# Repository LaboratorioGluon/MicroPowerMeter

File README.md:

# MicroPowerMeter

This repo contains the Hardware design of my version of a low current meter (from nanoamperes to milliamperes).

More Info [Blog Entry](https://en.laboratoriogluon.com/projects/micropowermeter/).

## Capabilities

- 4 kSps
- 3 Ranges: nA, uA and mA.
- Automatic range switching
- USB connection.
- Low Burden Voltage:
    - 10 uV/nA 
    - 10 uV/uA
    - 10 uV/mA

## Electrical characteristics

- TBD

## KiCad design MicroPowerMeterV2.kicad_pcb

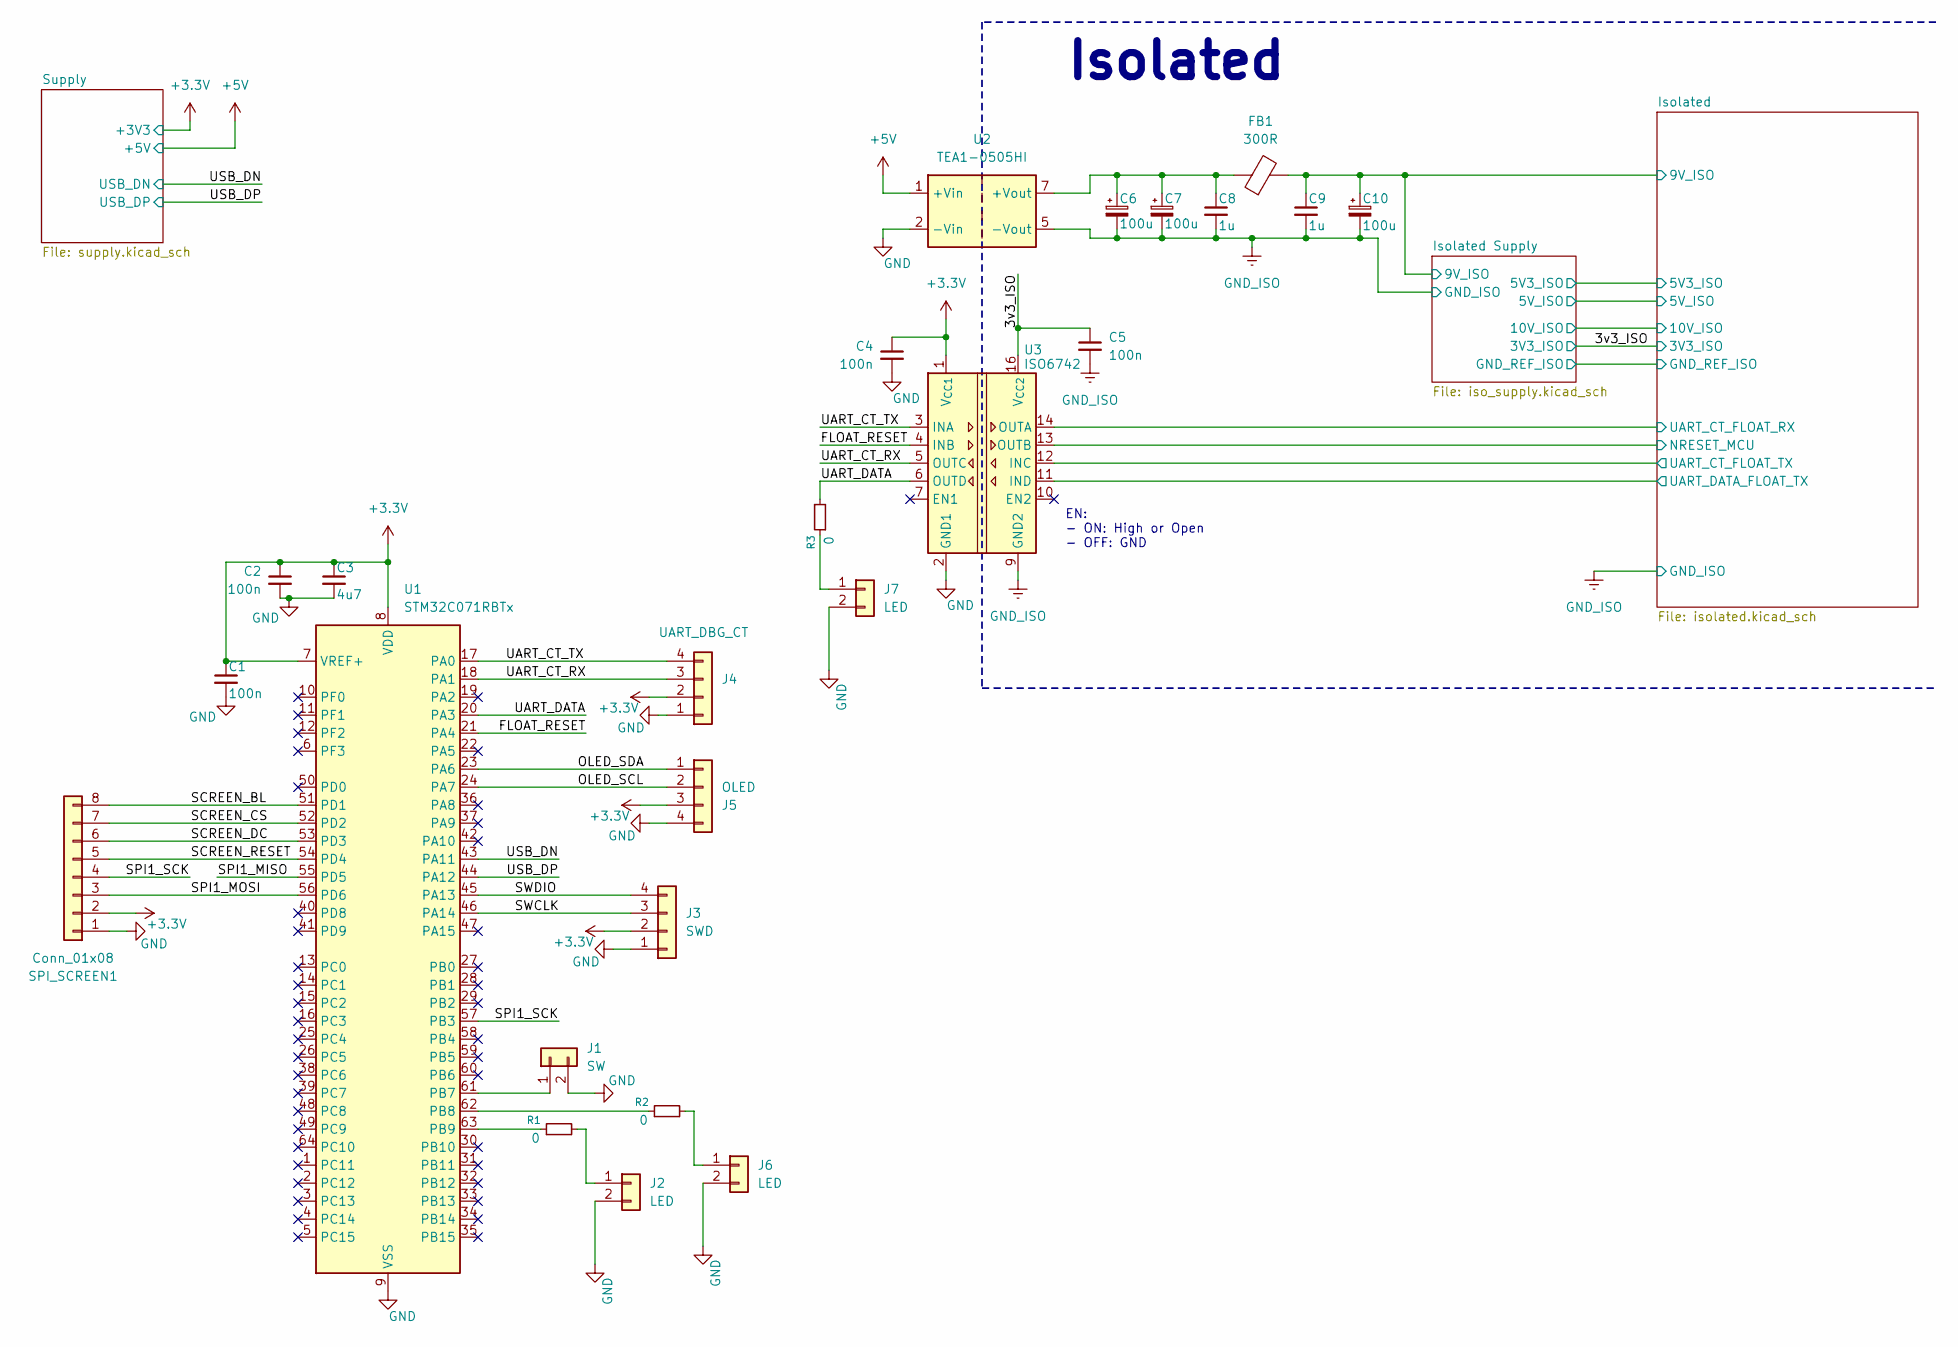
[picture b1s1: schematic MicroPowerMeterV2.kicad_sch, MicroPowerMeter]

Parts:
C1, C2, C4, C5: 100n; C_0603_1608Metric
C3: 4u7; C_0603_1608Metric
C6, C7: 100u; CP_Elec_6.3x5.4
C8, C9: 1u; C_0603_1608Metric
C10: 100u; C_0603_1608Metric
FB1: 300R; L_0603_1608Metric; PartNumber MMZ1608S301ATA00
J1: SW; PinHeader_1x02_P2.54mm_Vertical
J2, J6, J7: LED; PinHeader_1x02_P2.54mm_Vertical
J3: SWD; PinHeader_1x04_P2.54mm_Vertical
J4: UART_DBG_CT; PinHeader_1x04_P2.54mm_Vertical
J5: OLED; OLED_0.96_footprint
R1, R2, R3: 0; R_0603_1608Metric
SPI_SCREEN1: Conn_01x08; PinHeader_1x08_P2.54mm_Vertical
U1: STM32C071RBTx; LQFP-64_10x10mm_P0.5mm
U2: TEA1-0505HI; Converter_DCDC_TRACO_TEA1-xxxxHI_THT
U3: ISO6742; SOIC-16W_7.5x10.3mm_P1.27mm

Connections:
+3.3V: C1.1, C2.1, C3.1, C4.1, J3.2, J4.2, J5.3, SPI_SCREEN1.2, U1.7 (VREF+), U1.8 (VDD), U3.1 (V_{CC1}); also elsewhere on the board
+3V3_ISO: C5.1, U3.16 (V_{CC2}); also elsewhere on the board
+5V: U2.1 (+Vin); also elsewhere on the board
/FLOAT_RESET: U1.21 (PA4), U3.4 (INB)
/Isolated/9V_ISO: C9.1, C10.1, FB1.2; also elsewhere on the board
/Isolated/NRESET_MCU: U3.13 (OUTB); also elsewhere on the board
/Isolated/UART_CT_FLOAT_RX: U3.14 (OUTA); also elsewhere on the board
/Isolated/UART_CT_FLOAT_TX: U3.12 (INC); also elsewhere on the board
/Isolated/UART_DATA_FLOAT_TX: U3.11 (IND); also elsewhere on the board
/OLED_SCL: J5.2, U1.24 (PA7)
/OLED_SDA: J5.1, U1.23 (PA6)
/SCREEN_BL: SPI_SCREEN1.8, U1.51 (PD1)
/SCREEN_CS: SPI_SCREEN1.7, U1.52 (PD2)
/SCREEN_DC: SPI_SCREEN1.6, U1.53 (PD3)
/SCREEN_RESET: SPI_SCREEN1.5, U1.54 (PD4)
/SPI1_MISO: U1.55 (PD5)
/SPI1_MOSI: SPI_SCREEN1.3, U1.56 (PD6)
/SPI1_SCK: SPI_SCREEN1.4, U1.57 (PB3)
/SWCLK: J3.3, U1.46 (PA14)
/SWDIO: J3.4, U1.45 (PA13)
/UART_CT_RX: J4.3, U1.18 (PA1), U3.5 (OUTC)
/UART_CT_TX: J4.4, U1.17 (PA0), U3.3 (INA)
/UART_DATA: R3.2, U1.20 (PA3), U3.6 (OUTD)
/USB_DN: U1.43 (PA11); also elsewhere on the board
/USB_DP: U1.44 (PA12); also elsewhere on the board
GND: C1.2, C2.2, C3.2, C4.2, J1.2, J2.2, J3.1, J4.1, J5.4, J6.2, J7.2, SPI_SCREEN1.1, U1.9 (VSS), U2.2 (-Vin), U3.2 (GND1), U3.8 (GND1); also elsewhere on the board
GND_ISO: C5.2, C6.2, C7.2, C8.2, C9.2, C10.2, U2.5 (-Vout), U3.9 (GND2), U3.15 (GND2); also elsewhere on the board
unnamed: J1.1, U1.61 (PB7)
unnamed: J2.1, R1.2
unnamed: J6.1, R2.2
unnamed: J7.1, R3.1
unnamed: R2.1, U1.62 (PB8)
unnamed: R1.1, U1.63 (PB9)
unnamed: C6.1, C7.1, C8.1, FB1.1, U2.7 (+Vout)

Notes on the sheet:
Isolated
EN: - ON: High or Open - OFF: GND

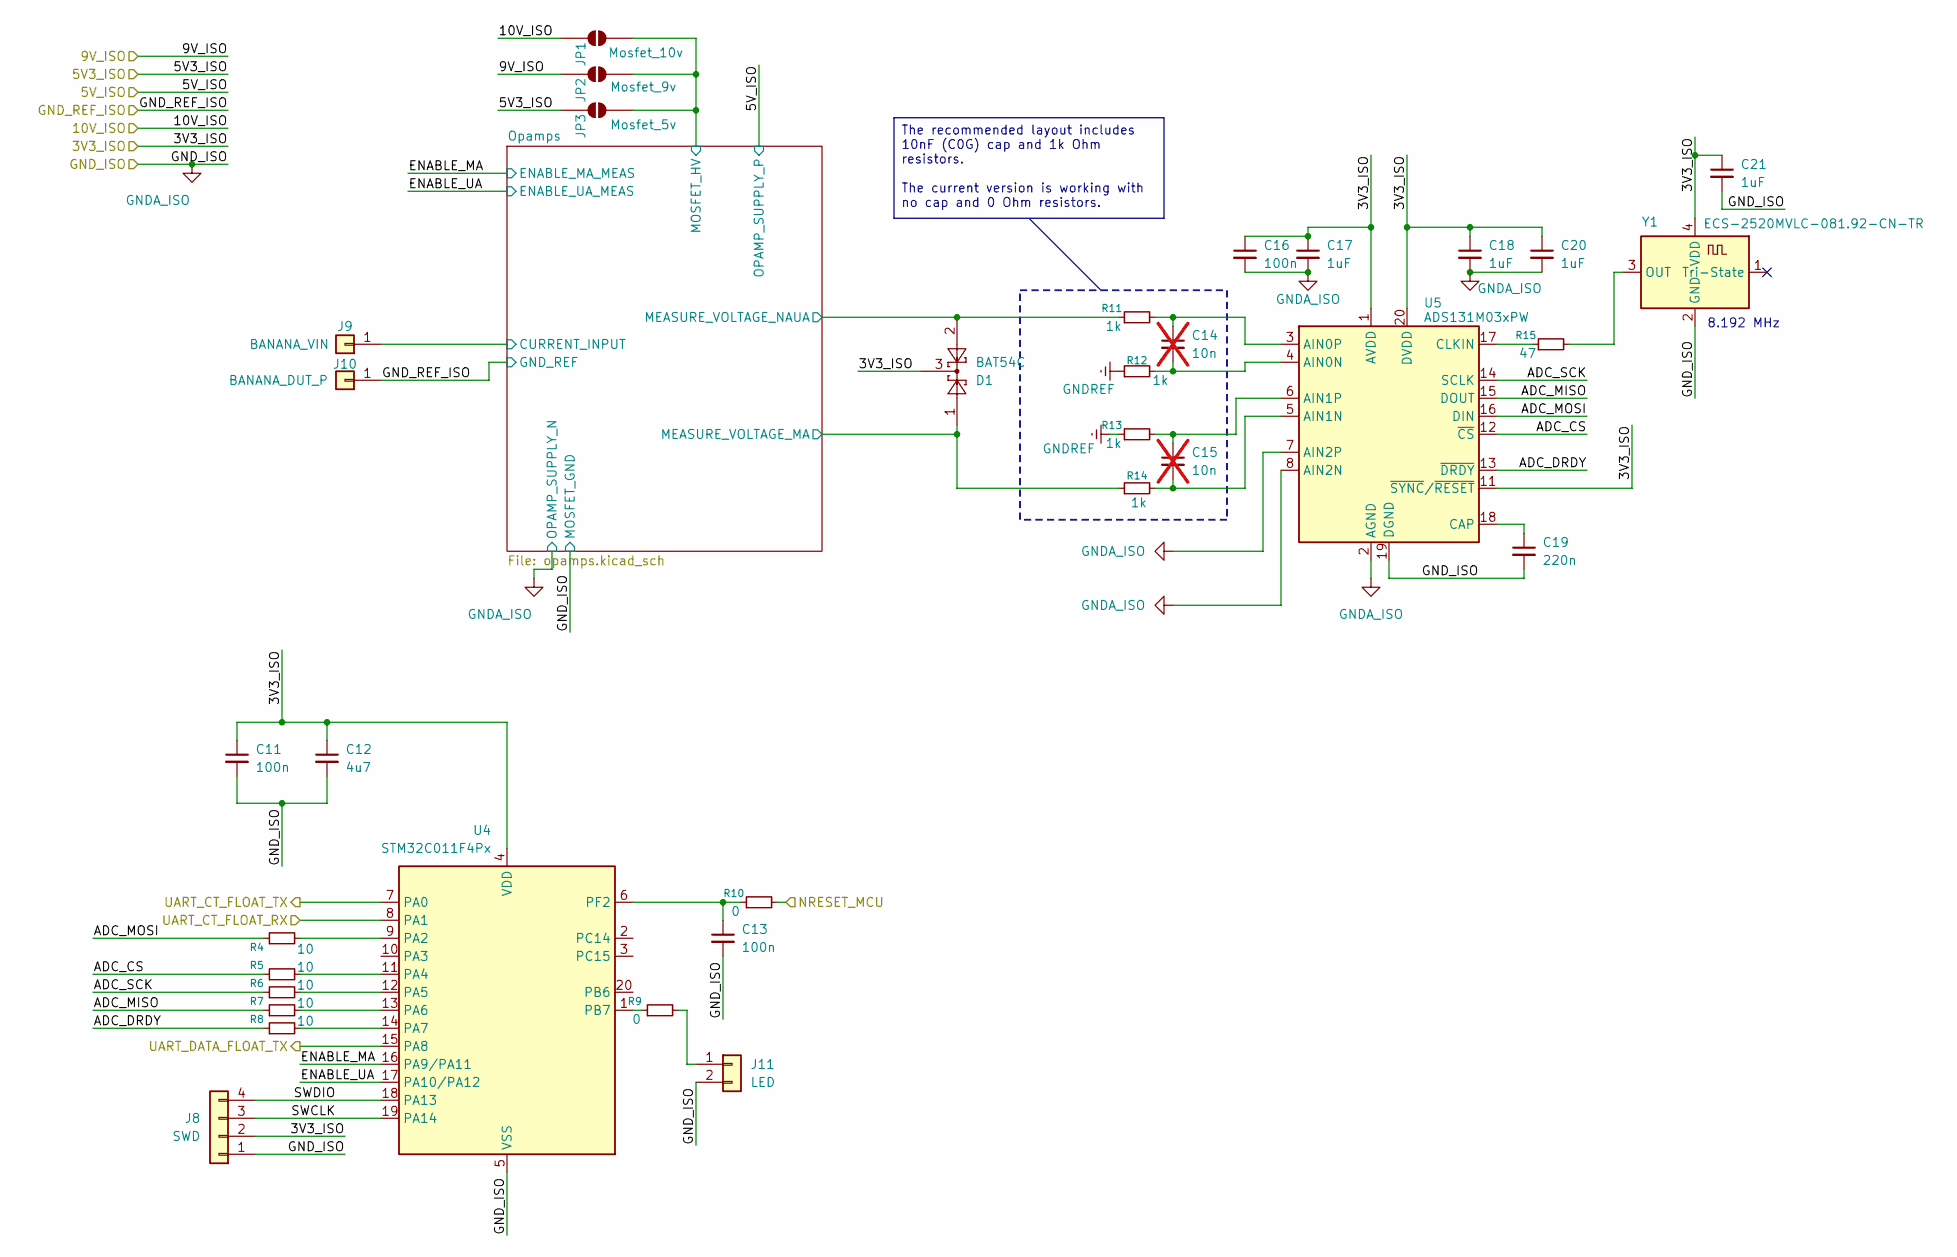
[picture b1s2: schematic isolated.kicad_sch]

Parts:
C11, C13, C16: 100n; C_0603_1608Metric_Pad1.08x0.95mm_HandSolder
C12: 4u7; C_0603_1608Metric_Pad1.08x0.95mm_HandSolder
C14, C15: 10n; C_0603_1608Metric_Pad1.08x0.95mm_HandSolder; not fitted
C17, C18, C20, C21: 1uF; C_0603_1608Metric_Pad1.08x0.95mm_HandSolder
C19: 220n; C_0603_1608Metric_Pad1.08x0.95mm_HandSolder
D1: BAT54C; SOT-23
J8: SWD; PinHeader_1x04_P2.54mm_Vertical
J9: BANANA_VIN; SolderWirePad_1x01_SMD_4x8mm
J10: BANANA_DUT_P; SolderWirePad_1x01_SMD_4x8mm
J11: LED; PinHeader_1x02_P2.54mm_Vertical
JP1: Mosfet_10v; SolderJumper-2_P1.3mm_Open_RoundedPad1.0x1.5mm
JP2: Mosfet_9v; SolderJumper-2_P1.3mm_Open_RoundedPad1.0x1.5mm
JP3: Mosfet_5v; SolderJumper-2_P1.3mm_Open_RoundedPad1.0x1.5mm
R4, R5, R6, R7, R8: 10; R_0603_1608Metric
R9, R10: 0; R_0603_1608Metric
R11, R12, R13, R14: 1k; R_0603_1608Metric
R15: 47; R_0603_1608Metric
U4: STM32C011F4Px; TSSOP-20_4.4x6.5mm_P0.65mm
U5: ADS131M03xPW; TSSOP-20_4.4x6.5mm_P0.65mm
Y1: ECS-2520MVLC-081.92-CN-TR; Oscillator_SMD_ECS_2520MV-xxx-xx-4Pin_2.5x2.0mm

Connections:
+3V3_ISO: C11.1, C12.1, C16.1, C17.1, C18.1, C20.1, C21.1, D1.3, J8.2, U4.4 (VDD), U5.1 (AVDD), U5.11 (~SYNC/~RESET), U5.20 (DVDD), Y1.4 (VDD); also elsewhere on the board
+10V_ISO: JP1.2 (B); also elsewhere on the board
/Isolated Supply/5V3_ISO: JP3.2 (B); also elsewhere on the board
/Isolated/9V_ISO: JP2.2 (B); also elsewhere on the board
/Isolated/ADC_CS: R5.1, U5.12 (~CS)
/Isolated/ADC_DRDY: R8.1, U5.13 (~DRDY)
/Isolated/ADC_MISO: R7.1, U5.15 (DOUT)
/Isolated/ADC_MOSI: R4.1, U5.16 (DIN)
/Isolated/ADC_SCK: R6.1, U5.14 (SCLK)
/Isolated/ENABLE_MA: U4.16 (PA9/PA11); also elsewhere on the board
/Isolated/ENABLE_UA: U4.17 (PA10/PA12); also elsewhere on the board
/Isolated/NRESET_MCU: R10.2; also elsewhere on the board
/Isolated/Opamps/CURRENT_INPUT: J9.1 (Pin_1_1); also elsewhere on the board
/Isolated/Opamps/MEASURE_VOLTAGE_MA: D1.1, R14.1; also elsewhere on the board
/Isolated/Opamps/MEASURE_VOLTAGE_NAUA: D1.2, R11.1; also elsewhere on the board
/Isolated/Opamps/MOSFET_HV: JP1.1 (A), JP2.1 (A), JP3.1 (A); also elsewhere on the board
/Isolated/SWCLK: J8.3, U4.19 (PA14)
/Isolated/SWDIO: J8.4, U4.18 (PA13)
/Isolated/UART_CT_FLOAT_RX: U4.8 (PA1); also elsewhere on the board
/Isolated/UART_CT_FLOAT_TX: U4.7 (PA0); also elsewhere on the board
/Isolated/UART_DATA_FLOAT_TX: U4.15 (PA8); also elsewhere on the board
GNDREF: J10.1 (Pin_1_1), R12.1, R13.1; also elsewhere on the board
GND_ISO: C11.2, C12.2, C13.2, C16.2, C17.2, C18.2, C19.2, C20.2, C21.2, J8.1, J11.2, U4.5 (VSS), U5.2 (AGND), U5.7 (AIN2P), U5.8 (AIN2N), U5.19 (DGND), Y1.2 (GND); also elsewhere on the board
unnamed: J11.1, R9.2
unnamed: R4.2, U4.9 (PA2)
unnamed: R5.2, U4.11 (PA4)
unnamed: R6.2, U4.12 (PA5)
unnamed: R7.2, U4.13 (PA6)
unnamed: R8.2, U4.14 (PA7)
unnamed: R9.1, U4.1 (PB7)
unnamed: C13.1, R10.1, U4.6 (PF2)
unnamed: C14.2, R12.2, U5.4 (AIN0N)
unnamed: C14.1, R11.2, U5.3 (AIN0P)
unnamed: C15.2, R14.2, U5.5 (AIN1N)
unnamed: C15.1, R13.2, U5.6 (AIN1P)
unnamed: C19.1, U5.18 (CAP)
unnamed: R15.1, U5.17 (CLKIN)
unnamed: R15.2, Y1.3 (OUT)

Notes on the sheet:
8.192 MHz
The recommended layout includes 10nF (C0G) cap and 1k Ohm resistors. The current version is working with no cap and 0 Ohm resistors.

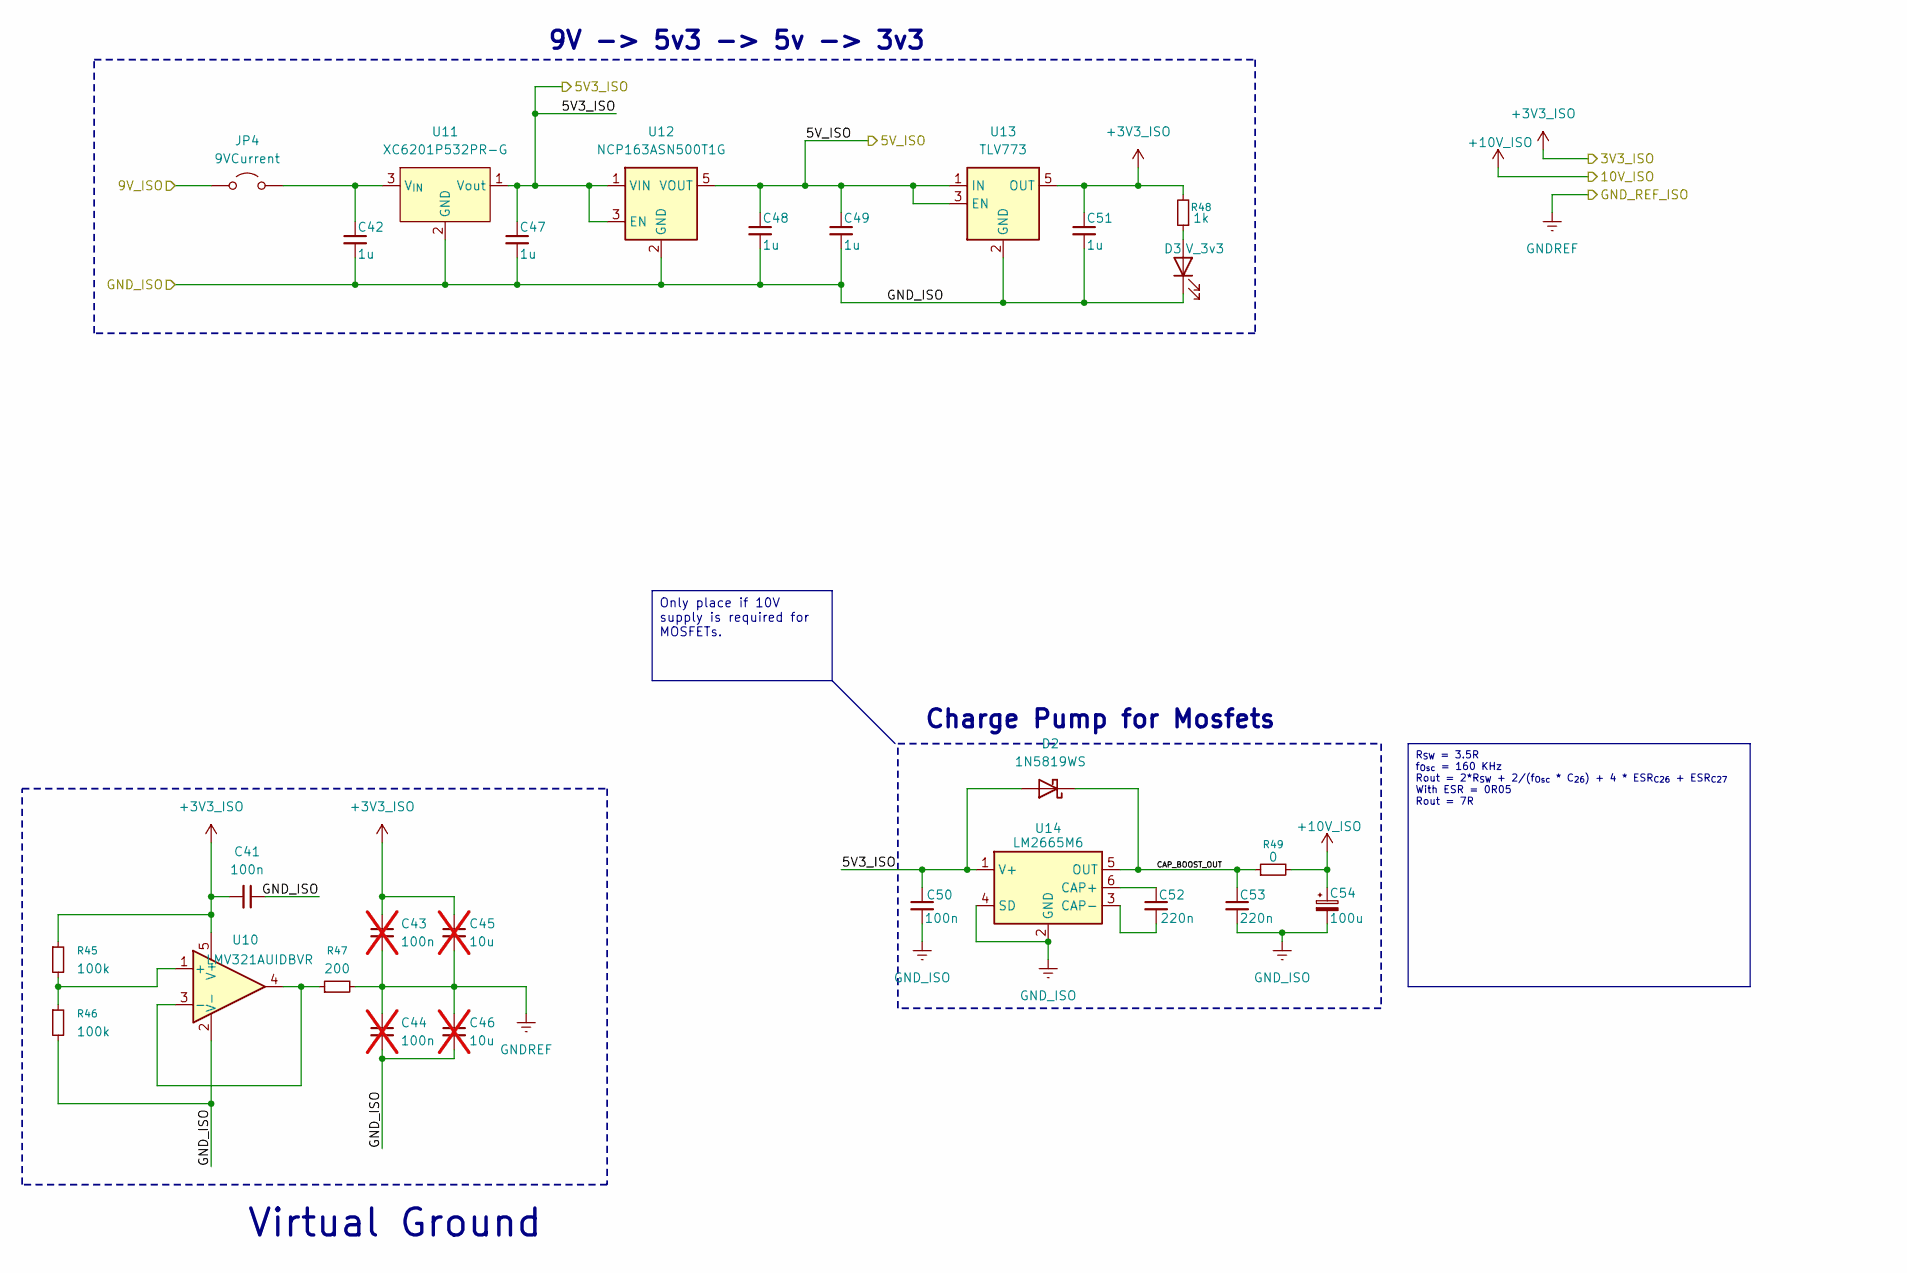
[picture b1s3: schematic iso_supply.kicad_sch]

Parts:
C41, C50: 100n; C_0603_1608Metric
C42, C47, C48, C49, C51: 1u; C_0603_1608Metric
C43, C44: 100n; C_0603_1608Metric; not fitted
C45, C46: 10u; C_0603_1608Metric; not fitted
C52, C53: 220n; C_0603_1608Metric
C54: 100u; CP_Elec_6.3x5.4
D2: 1N5819WS; D_SOD-323_HandSoldering
D3: V_3v3; LED_0603_1608Metric
JP4: 9VCurrent; PinHeader_1x02_P2.54mm_Vertical
R45, R46: 100k; R_0603_1608Metric
R47: 200; R_0603_1608Metric
R48: 1k; R_0603_1608Metric
R49: 0; R_0603_1608Metric
U10: LMV321AUIDBVR; SOT-23-5
U11: XC6201P532PR-G; SOT-89-3
U12: NCP163ASN500T1G; SOT-23-5
U13: TLV773; SOT-23-5
U14: LM2665M6; SOT-23-6; PartNumber LM2665M6X/NOPB

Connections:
+3V3_ISO: C41.2, C43.1, C45.1, C51.1, R45.1, R48.2, U10.5 (V+), U13.5 (OUT); also elsewhere on the board
+10V_ISO: C54.1, R49.2; also elsewhere on the board
/Isolated Supply/5V3_ISO: C47.1, C50.1, D2.2 (A), U11.1 (Vout), U12.1 (VIN), U12.3 (EN), U14.1 (V+); also elsewhere on the board
/Isolated Supply/5V_ISO: C48.1, C49.1, U12.5 (VOUT), U13.1 (IN), U13.3 (EN); also elsewhere on the board
/Isolated Supply/CAP_BOOST_OUT: C53.1, D2.1 (K), R49.1, U14.5 (OUT)
/Isolated/9V_ISO: JP4.1 (A); also elsewhere on the board
GNDREF: C43.2, C44.1, C45.2, C46.1, R47.2; also elsewhere on the board
GND_ISO: C41.1, C42.2, C44.2, C46.2, C47.2, C48.2, C49.2, C50.2, C51.2, C53.2, C54.2, D3.1 (K), R46.2, U10.2 (V-), U11.2 (GND), U12.2 (GND), U13.2 (GND), U13.4 (GND), U14.2 (GND), U14.4 (SD); also elsewhere on the board
unnamed: D3.2 (A), R48.1
unnamed: C42.1, JP4.2 (B), U11.3 (V_{IN})
unnamed: R45.2, R46.1, U10.1 (+)
unnamed: R47.1, U10.3 (-), U10.4
unnamed: C52.1, U14.6 (CAP+)
unnamed: C52.2, U14.3 (CAP-)

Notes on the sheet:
9V -> 5v3 -> 5v -> 3v3
Virtual Ground
Charge Pump for Mosfets
R_{SW} = 3.5R f_{Osc} = 160 KHz Rout = 2*R_{SW} + 2/(f_{Osc} * C_{26}) + 4 * ESR_{C26} + ESR_{C27} With ESR = 0R05 Rout = 7R
Only place if 10V supply is required for MOSFETs.

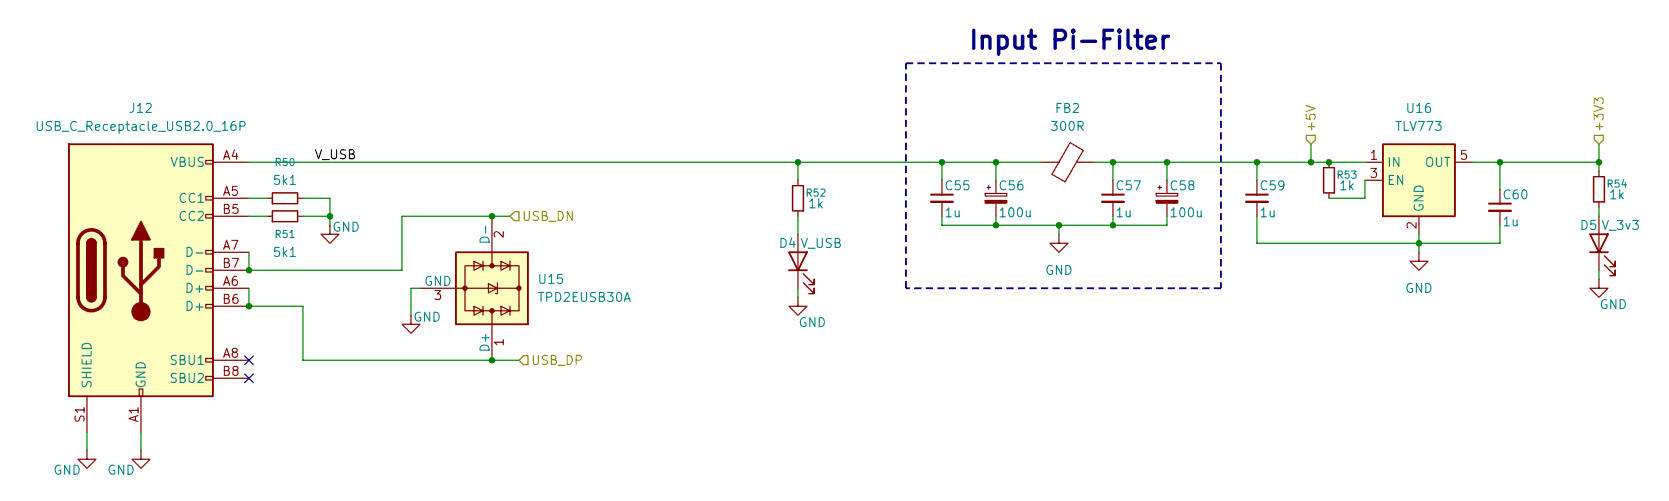
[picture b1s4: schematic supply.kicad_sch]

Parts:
C55, C57, C59, C60: 1u; C_0603_1608Metric
C56, C58: 100u; C_0603_1608Metric
D4: V_USB; LED_0603_1608Metric
D5: V_3v3; LED_0603_1608Metric
FB2: 300R; L_0603_1608Metric; PartNumber MMZ1608S301ATA00
J12: USB_C_Receptacle_USB2.0_16P; USB_C_Receptacle_GCT_USB4105-xx-A_16P_TopMnt_Horizontal
R50, R51: 5k1; R_0603_1608Metric
R52, R53, R54: 1k; R_0603_1608Metric
U15: TPD2EUSB30A; Texas_DRT-3
U16: TLV773; SOT-23-5

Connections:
+3.3V: C60.1, R54.2, U16.5 (OUT); also elsewhere on the board
+5V: C57.1, C58.1, C59.1, FB2.2, R53.2, U16.1 (IN); also elsewhere on the board
/Supply/V_USB: C55.1, C56.1, FB2.1, J12.A4 (VBUS), J12.A9 (VBUS), J12.B4 (VBUS), J12.B9 (VBUS), R52.2
/USB_DN: J12.A7 (D-), J12.B7 (D-), U15.2 (D-); also elsewhere on the board
/USB_DP: J12.A6 (D+), J12.B6 (D+), U15.1 (D+); also elsewhere on the board
GND: C55.2, C56.2, C57.2, C58.2, C59.2, C60.2, D4.1 (K), D5.1 (K), J12.A1 (GND), J12.A12 (GND), J12.B1 (GND), J12.B12 (GND), J12.S1 (SHIELD), R50.2, R51.2, U15.3 (GND), U16.2 (GND), U16.4 (GND); also elsewhere on the board
unnamed: D4.2 (A), R52.1
unnamed: D5.2 (A), R54.1
unnamed: J12.A5 (CC1), R50.1
unnamed: J12.B5 (CC2), R51.1
unnamed: R53.1, U16.3 (EN)

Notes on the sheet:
Input Pi-Filter

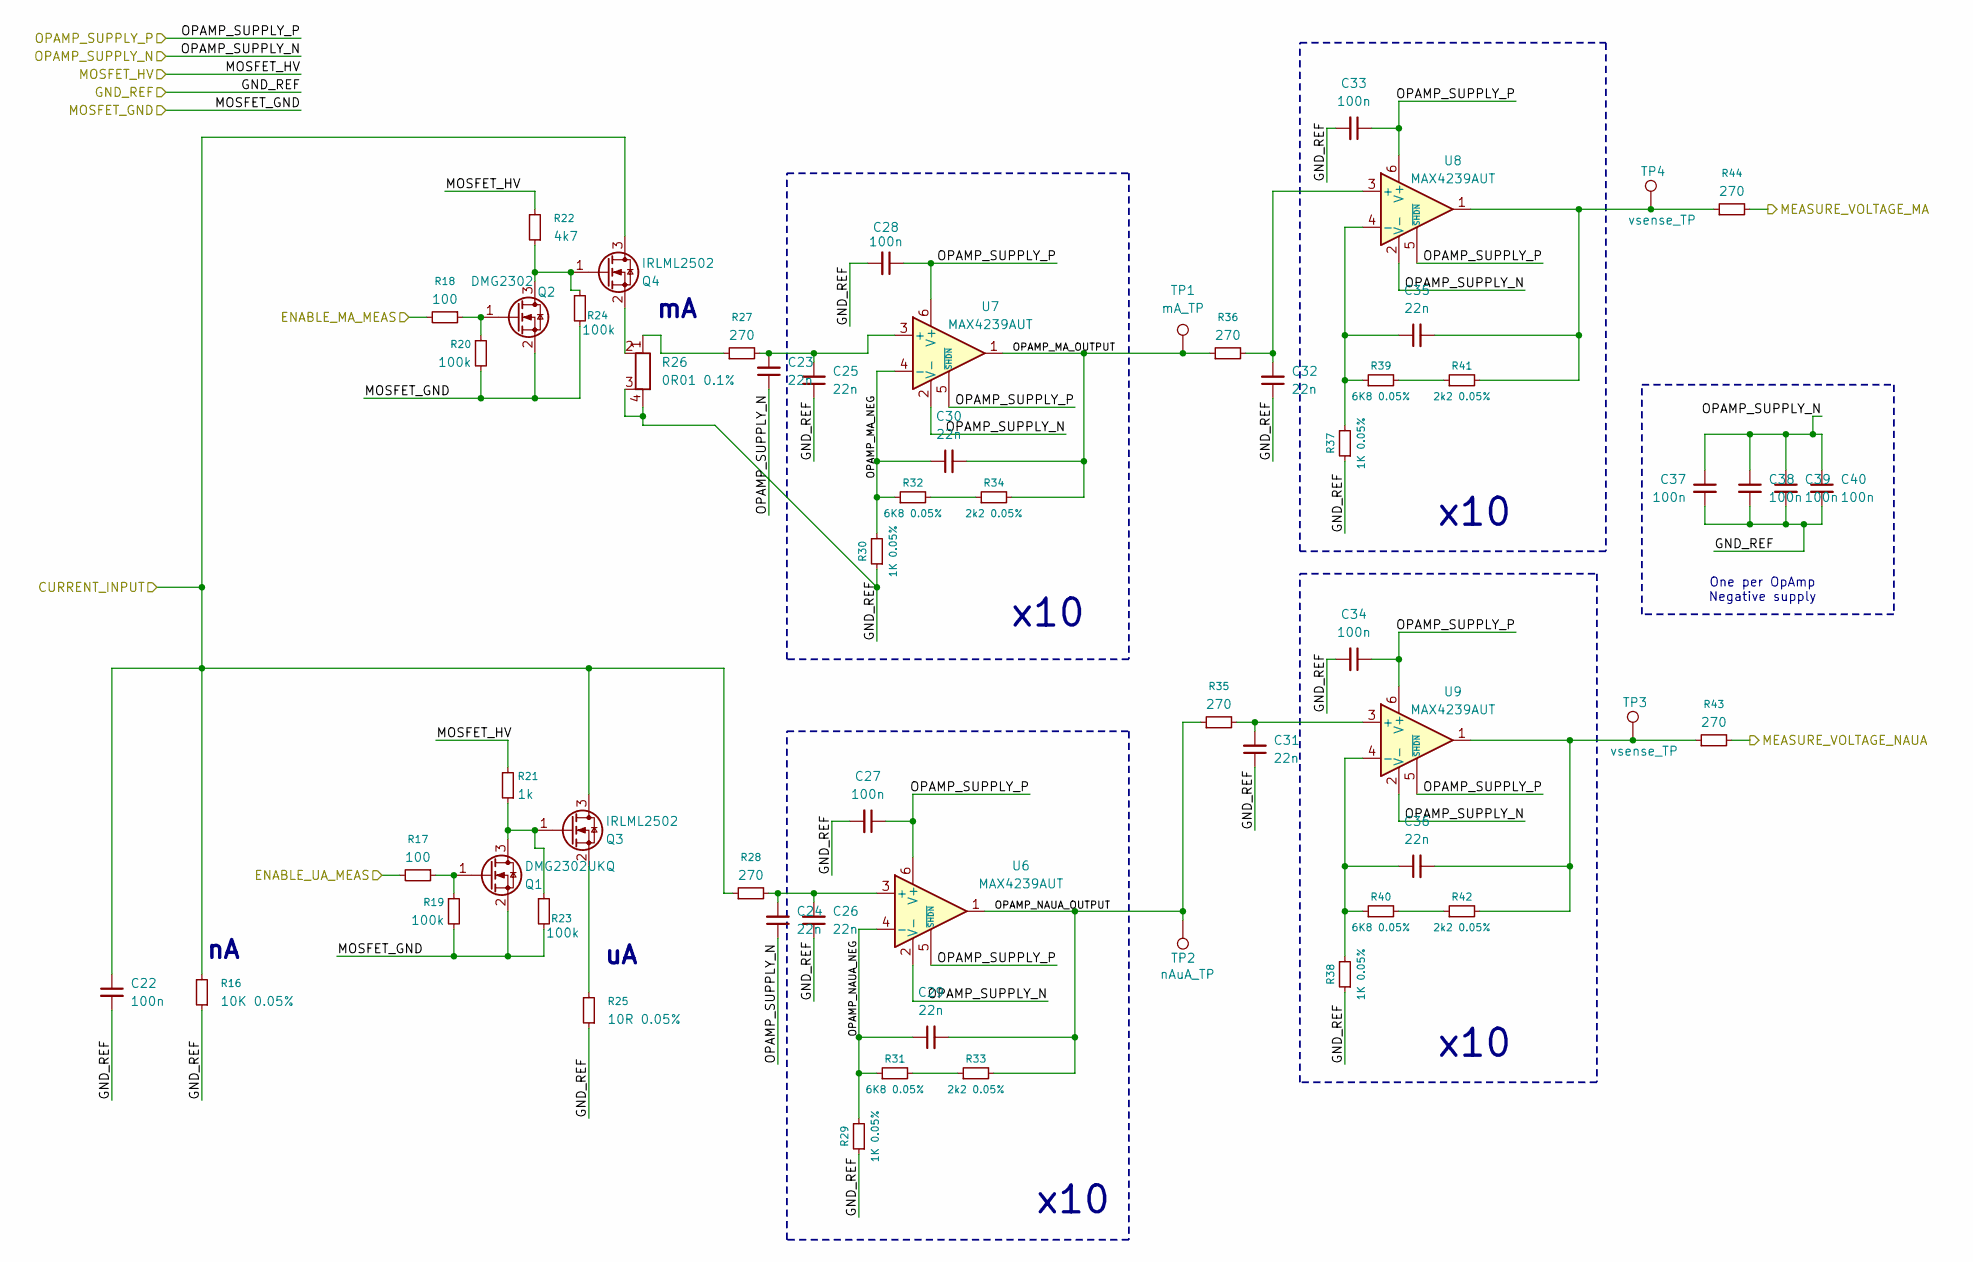
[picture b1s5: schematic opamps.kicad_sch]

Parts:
C22, C27, C28, C33, C34, C37, C38, C39, C40: 100n; C_0603_1608Metric
C23, C24, C25, C26, C29, C30, C31, C32, C35, C36: 22n; C_0603_1608Metric
Q1: DMG2302UKQ; SOT-23; PartNumber IRLML2502TRPBF
Q2: DMG2302; SOT-23; PartNumber IRLML2502TRPBF
Q3, Q4: IRLML2502; SOT-23; PartNumber IRLML2502TRPBF
R16: 10K 0.05%; R_0603_1608Metric; PartNumber RG1608N-103-W-T5
R17, R18: 100; R_0603_1608Metric
R19, R20, R23, R24: 100k; R_0603_1608Metric
R21: 1k; R_0603_1608Metric
R22: 4k7; R_0603_1608Metric
R25: 10R 0.05%; R_0603_1608Metric; PartNumber RNCF0603AKT10R0
R26: 0R01 0.1%; R_Shunt_Ohmite_LVK12; PartNumber LVK12R010DER
R27, R28, R35, R36, R43, R44: 270; R_0603_1608Metric
R29, R30, R37, R38: 1K 0.05%; R_0603_1608Metric; PartNumber RG1608N-102-W-T5
R31, R32, R39, R40: 6K8 0.05%; R_0603_1608Metric; PartNumber RG1608N-682-W-T1
R33, R34, R41, R42: 2k2 0.05%; R_0603_1608Metric; PartNumber RG1608N-222-W-T1
TP1: mA_TP; TestPoint_Pad_D1.0mm
TP2: nAuA_TP; TestPoint_Pad_D1.0mm
TP3, TP4: vsense_TP; TestPoint_Pad_D1.5mm
U6, U7, U8, U9: MAX4239AUT; SOT-23-6; PartNumber MAX4239AUT+T/OPA189IDBVR

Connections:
/Isolated Supply/5V_ISO: C27.1, C28.1, C33.1, C34.1, U6.5 (~SHDN), U6.6 (V+), U7.5 (~SHDN), U7.6 (V+), U8.5 (~SHDN), U8.6 (V+), U9.5 (~SHDN), U9.6 (V+); also elsewhere on the board
/Isolated/ENABLE_MA: R18.2; also elsewhere on the board
/Isolated/ENABLE_UA: R17.2; also elsewhere on the board
/Isolated/Opamps/CURRENT_INPUT: C22.1, Q3.3 (D), Q4.3 (D), R16.2, R28.1; also elsewhere on the board
/Isolated/Opamps/MEASURE_VOLTAGE_MA: R44.2; also elsewhere on the board
/Isolated/Opamps/MEASURE_VOLTAGE_NAUA: R43.2; also elsewhere on the board
/Isolated/Opamps/MOSFET_HV: R21.2, R22.2; also elsewhere on the board
/Isolated/Opamps/OPAMP_MA_NEG: C30.1, R30.2, R32.1, U7.4 (-)
/Isolated/Opamps/OPAMP_MA_OUTPUT: C30.2, R34.2, R36.1, TP1.1 (1_1), U7.1
/Isolated/Opamps/OPAMP_NAUA_NEG: C29.1, R29.2, R31.1, U6.4 (-)
/Isolated/Opamps/OPAMP_NAUA_OUTPUT: C29.2, R33.2, R35.1, TP2.1 (1_1), U6.1
GNDREF: C22.2, C25.1, C26.1, C27.2, C28.2, C31.1, C32.1, C33.2, C34.2, C37.2, C38.2, C39.2, C40.2, R16.1, R25.1, R26.3, R26.4, R29.1, R30.1, R37.1, R38.1; also elsewhere on the board
GND_ISO: C23.1, C24.1, C37.1, C38.1, C39.1, C40.1, Q1.2 (S), Q2.2 (S), R19.2, R20.2, R23.2, R24.2, U6.2 (V-), U7.2 (V-), U8.2 (V-), U9.2 (V-); also elsewhere on the board
unnamed: C35.2, R41.2, R44.1, TP4.1 (1_1), U8.1
unnamed: C36.2, R42.2, R43.1, TP3.1 (1_1), U9.1
unnamed: Q1.3 (D), Q3.1 (G), R21.1, R23.1
unnamed: Q1.1 (G), R17.1, R19.1
unnamed: Q2.3 (D), Q4.1 (G), R22.1, R24.1
unnamed: Q2.1 (G), R18.1, R20.1
unnamed: Q3.2 (S), R25.2
unnamed: Q4.2 (S), R26.2
unnamed: R26.1, R27.1
unnamed: R31.2, R33.1
unnamed: R32.2, R34.1
unnamed: R39.2, R41.1
unnamed: R40.2, R42.1
unnamed: C24.2, C26.2, R28.2, U6.3 (+)
unnamed: C23.2, C25.2, R27.2, U7.3 (+)
unnamed: C32.2, R36.2, U8.3 (+)
unnamed: C35.1, R37.2, R39.1, U8.4 (-)
unnamed: C31.2, R35.2, U9.3 (+)
unnamed: C36.1, R38.2, R40.1, U9.4 (-)

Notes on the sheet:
x10
One per OpAmp Negative supply

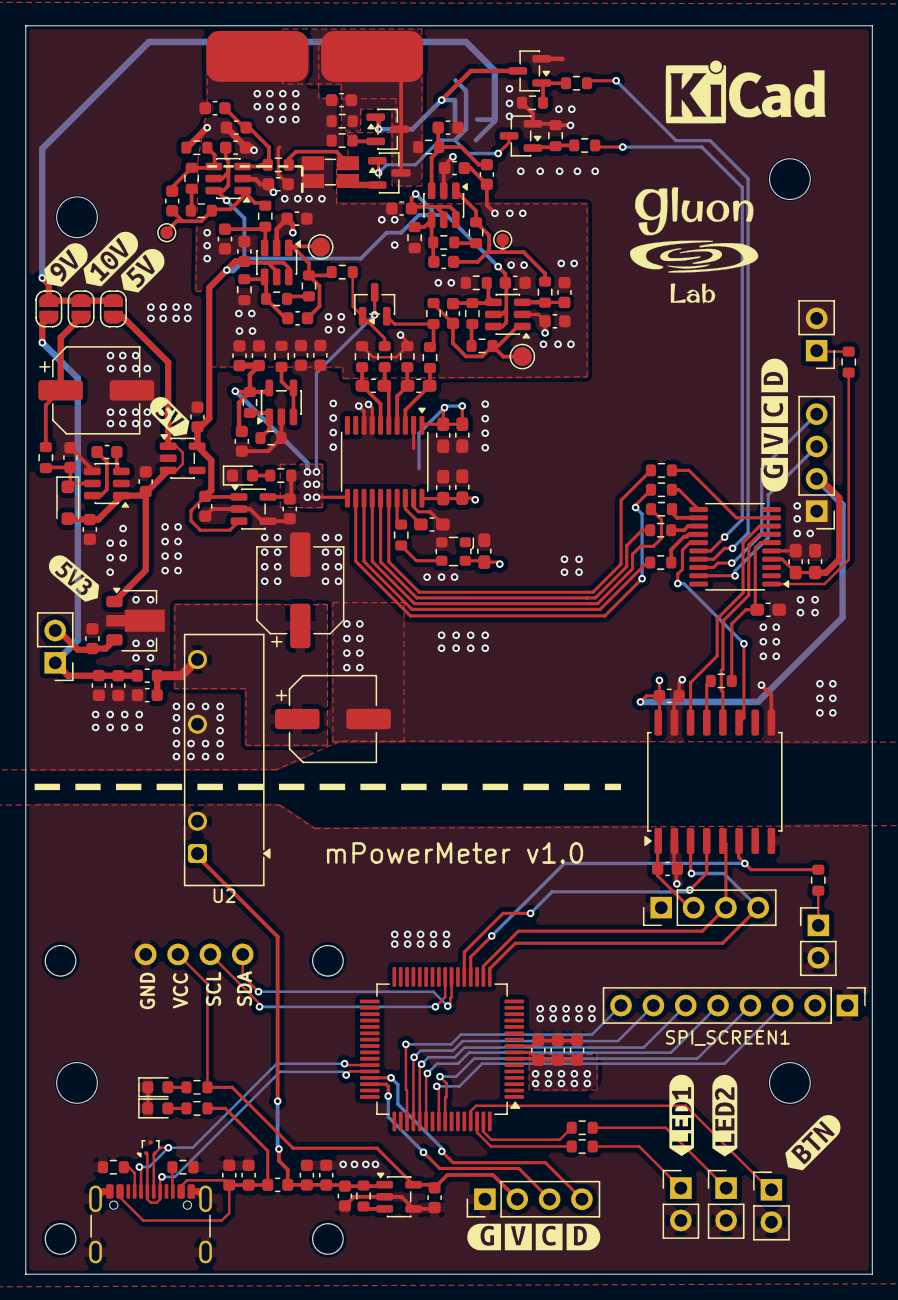
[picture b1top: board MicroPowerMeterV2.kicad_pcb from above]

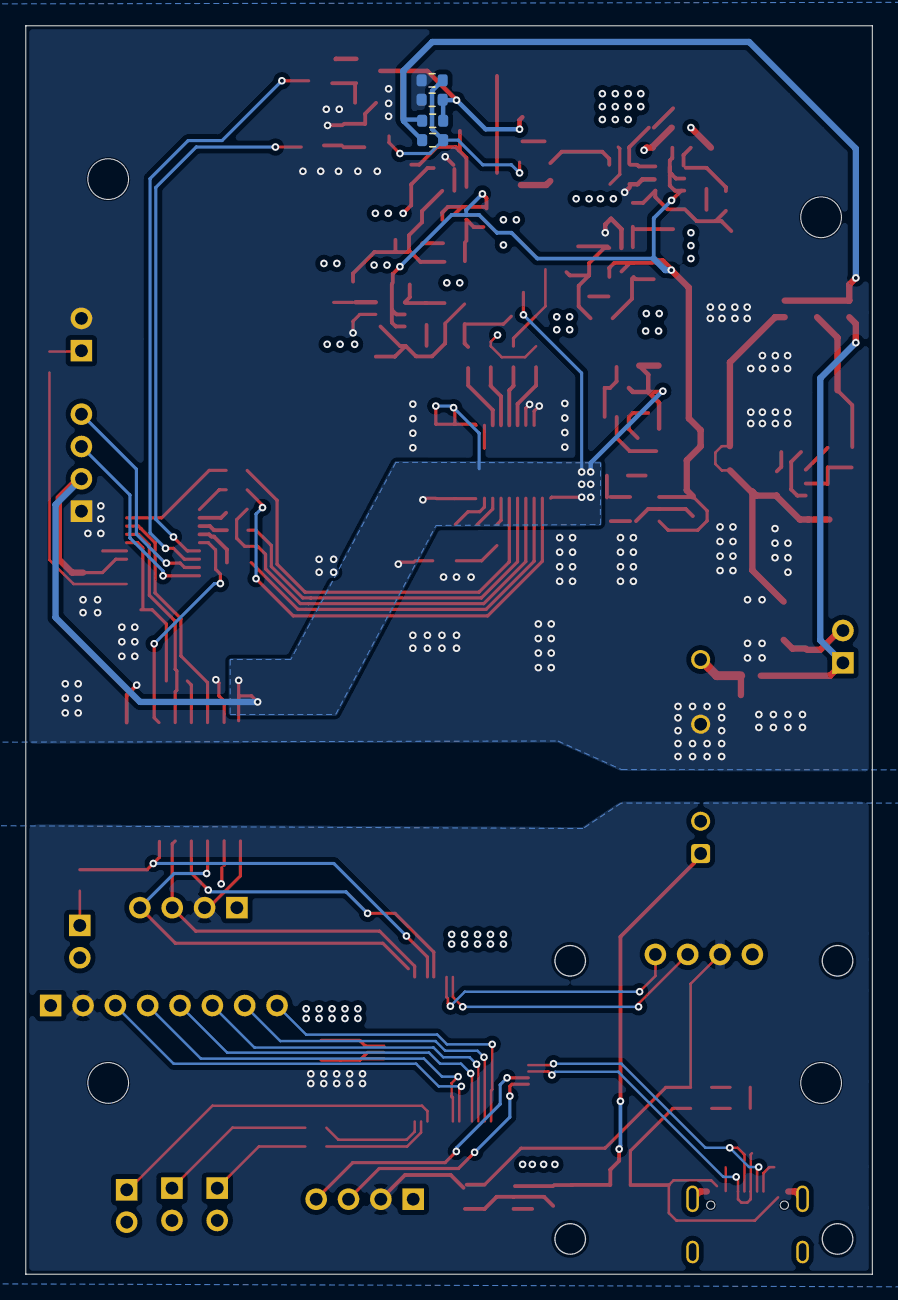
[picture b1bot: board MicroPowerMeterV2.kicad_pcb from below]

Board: 4 copper layers, 66.5 x 98.0 mm, 173 parts (4 on the bottom side), 101 nets.

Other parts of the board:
kibuzzard-69BFD08A: G***; kibuzzard-69BFD08A
kibuzzard-69BFD09C: G***; kibuzzard-69BFD09C
kibuzzard-69C15ACB: G***; kibuzzard-69C15ACB
kibuzzard-69C15AF6: G***; kibuzzard-69C15AF6
kibuzzard-69C042D6: G***; kibuzzard-69C042D6
kibuzzard-69C1593E: G***; kibuzzard-69C1593E
kibuzzard-69C1596C: G***; kibuzzard-69C1596C
kibuzzard-69C15949: G***; kibuzzard-69C15949
kibuzzard-693C2AD1: G***; kibuzzard-693C2AD1
kibuzzard-698DE9F7: G***; kibuzzard-698DE9F7

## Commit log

2026-06-24 Release V1.0
2026-06-24 Add GNU Lesser General Public License v2.1
    Added the GNU Lesser General Public License version 2.1 to the project.
2026-06-24 Created README.md
2026-06-24 Updated pdf
